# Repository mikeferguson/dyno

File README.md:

# dyno

Control code for my motor dyno

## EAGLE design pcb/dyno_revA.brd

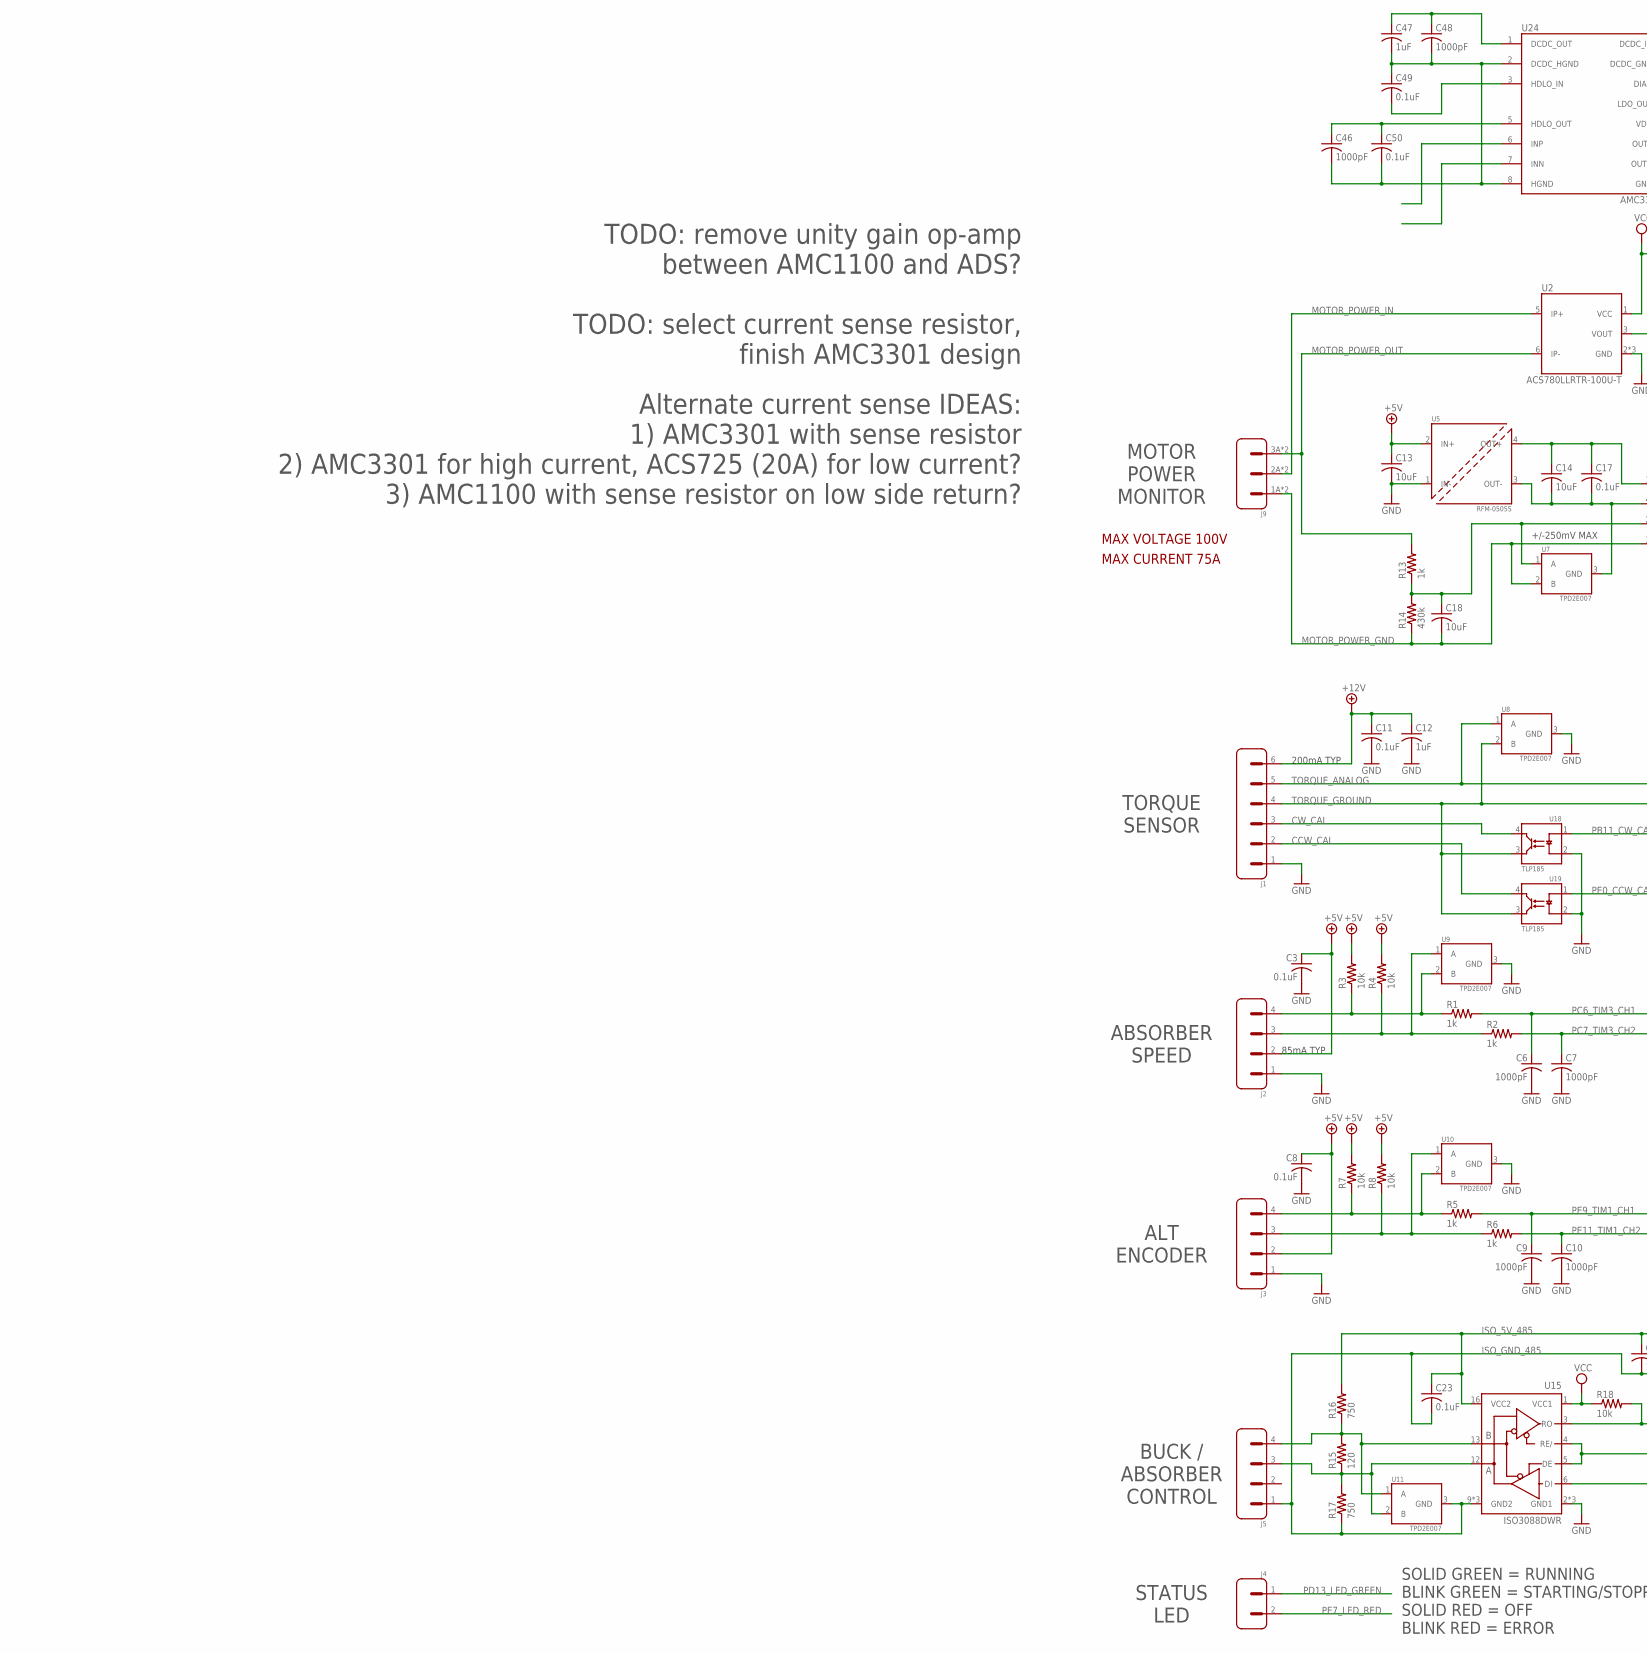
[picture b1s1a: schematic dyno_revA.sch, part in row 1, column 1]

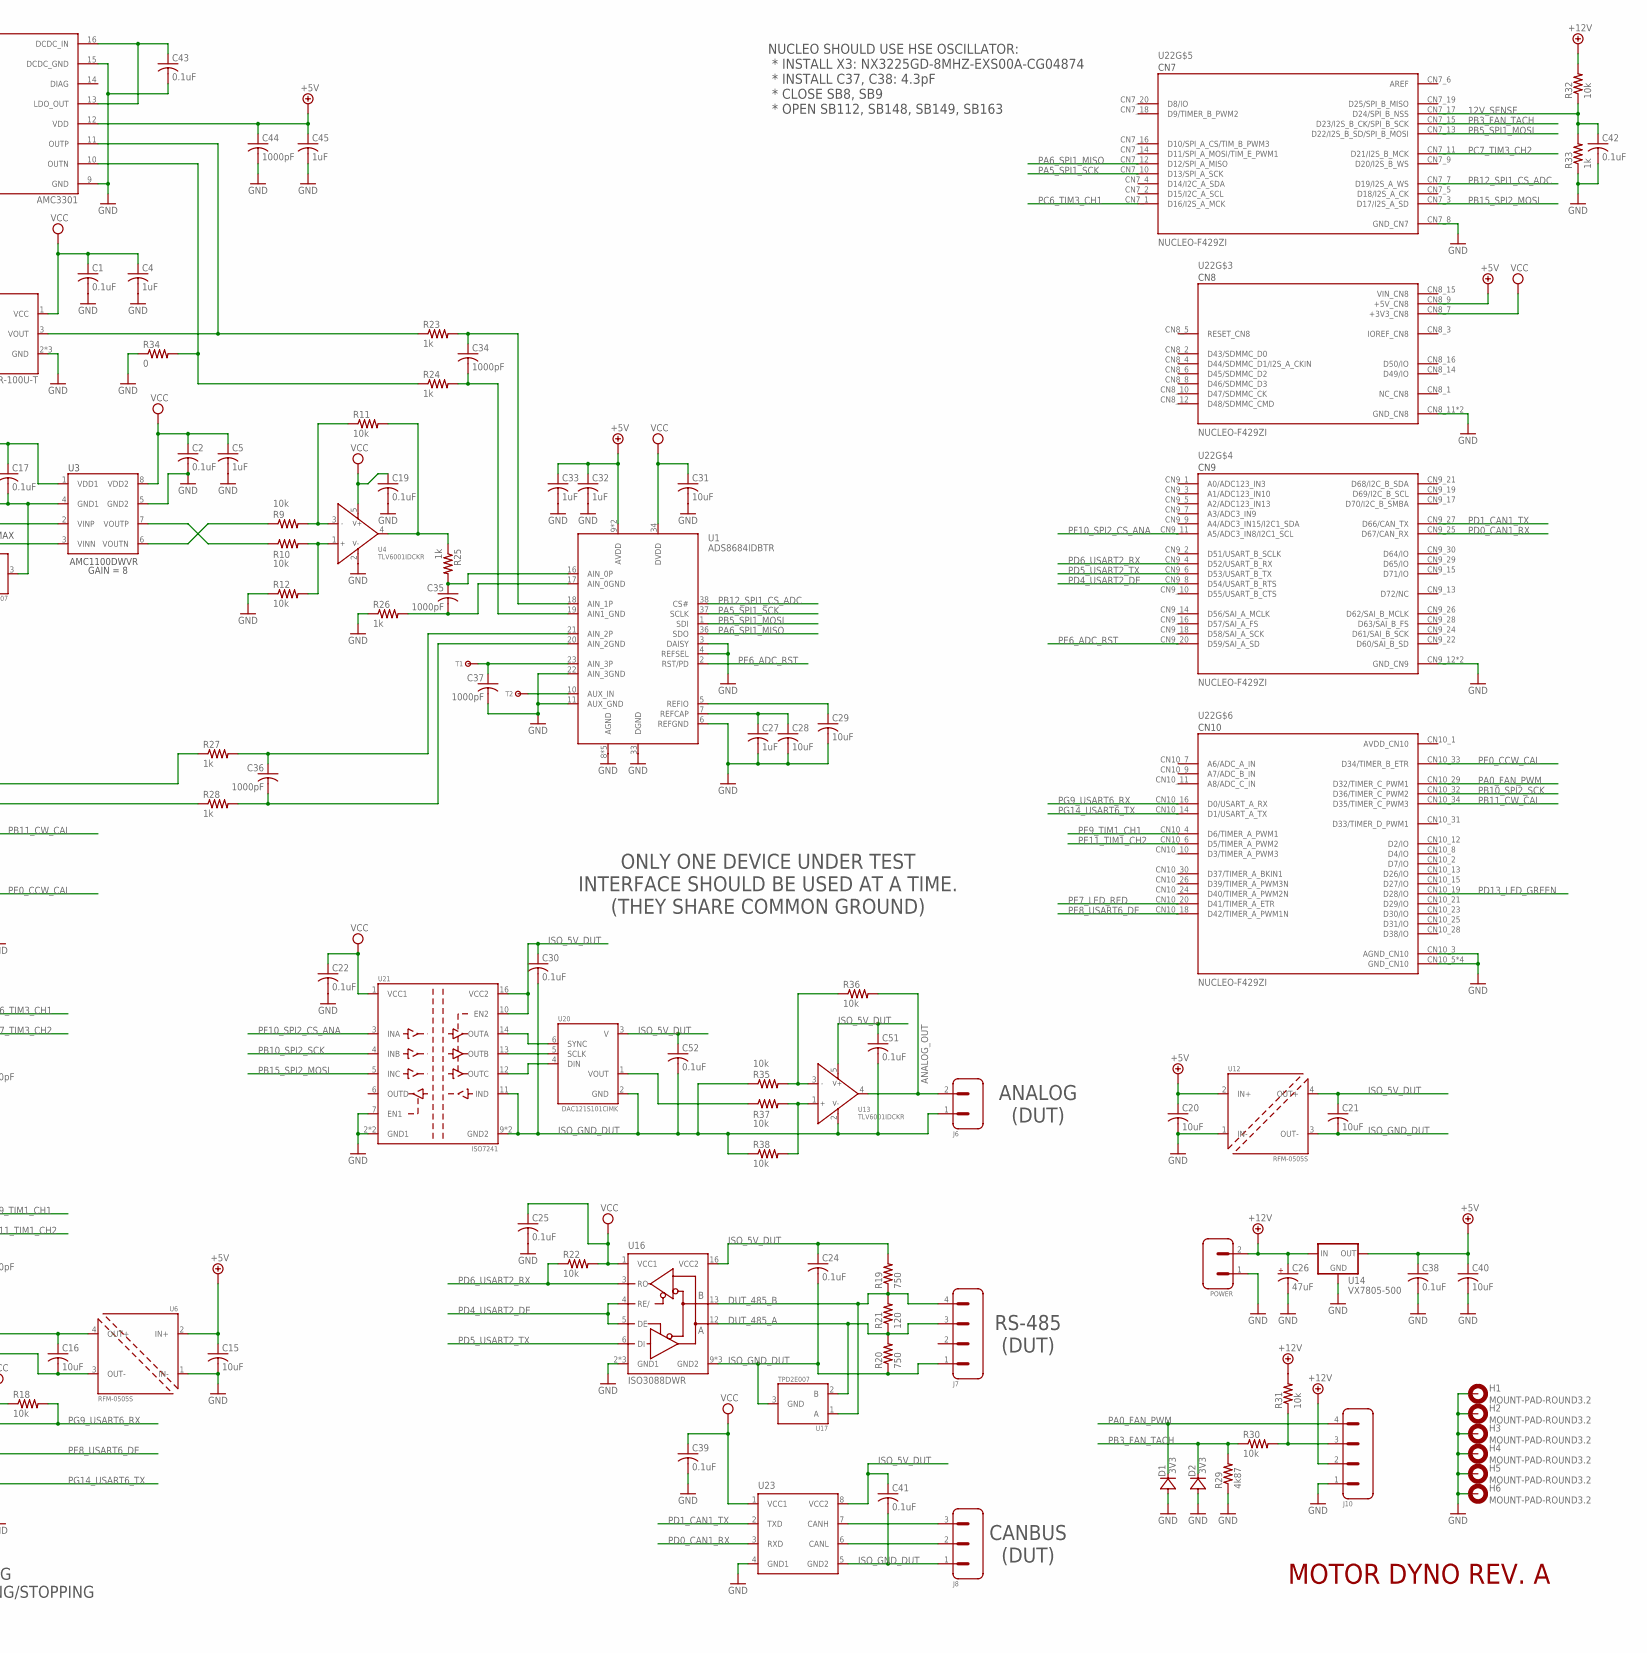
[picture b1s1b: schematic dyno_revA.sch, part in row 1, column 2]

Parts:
C1, C2, C3, C8, C11, C17, C19, C22, C23, C24, C25, C30, C38, C39, C41, C42, C43, C49, C50, C51, C52: 0.1uF; CAPC1608X90(C0603)
C4, C5, C12, C27, C32, C33, C45, C47: 1uF; CAPC1608X90(C0603)
C6, C7, C9, C10, C34, C35, C36, C37, C44, C46, C48: 1000pF; CAPC1608X90(C0603)
C13, C14, C15, C16, C18, C20, C21, C40: 10uF; CAPC2012X145
C26: 47uF; CAPAE830X850(PANA_F)
C28, C29, C31: 10uF; CAPC1608X90(C0603)
D1, D2: 3V3; SOD2513X110(SOD323)
H1, H2, H3, H4, H5, H6: MOUNT-PAD-ROUND3.2; 3,2-PAD
J1: 502584-0670
J2, J3: 502584-0470
J4, J6: 502584-0270
J5, J7: 43650-0416
J8: 43650-0316
J9: 1017532
J10: 22-23-2041
POWER: 39-29-0023; 5566-2
R1, R2, R5, R6, R13, R23, R24, R25, R26, R27, R28, R33: 1k; RESC1608X55(ERJ-0603)
R3, R4, R7, R8, R9, R10, R11, R12, R18, R22, R30, R31, R32, R35, R36, R37, R38: 10k; RESC1608X55(ERJ-0603)
R14: 430k; RESC1608X55(ERJ-0603)
R15, R21: 120; RESC1608X55(ERJ-0603)
R16, R17, R19, R20: 750; RESC1608X55(ERJ-0603)
R29: 4k87; RESC1608X55(ERJ-0603)
R34: 0; RESC1608X55(ERJ-0603)
T1, T2: TESTPAD; TEST
U1: ADS8684IDBTR; SOP50P640X120-38
U2: ACS780LLRTR-100U-T; ACS780
U3: AMC1100DWVR; SOIC127P1150X280-8
U4, U13: TLV6001IDCKR; SOT65P210X110-5
U5, U6, U12: RFM-0505S; RFM
U7, U8, U9, U10, U11, U17: TPD2E007; SOT65P210X110-3(SOT323)
U14: VX7805-500; VX78-500
U15, U16: ISO3088DWR; SOIC127P1030X265-16
U18, U19: TLP185; SOT127P700X220-4
U20: DAC121S101CIMK; SOT95P280X110-6
U21: ISO7241; SOIC127P1030X265-16
U22: NUCLEO-F429ZI; MODULE_NUCLEO-F429ZI
U23: ISO1042DWVR; SOIC127P1150X265-8N
U24: AMC3301; SOIC127P1030X265-16N

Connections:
12V_SENSE: C42.1, R32.1, R33.2, U22.CN7_17 (D24/SPI_B_NSS)
+5V: C3.1, C8.1, C13.1, C15.1, C20.1, C32.1, C33.1, C38.1, C40.1, C44.1, C45.1, J2.2, J3.2, R3.2, R4.2, R7.2, R8.2, U1.9 (AVDD), U1.30 (AVDD), U5.2 (IN+), U6.2 (IN+), U12.2 (IN+), U14.3 (OUT), U22.CN8_9 (+5V_CN8), U24.12 (VDD)
+12V: C11.1, C12.1, C26.1 (+), J1.6, J10.2, POWER.2, R31.2, R32.2, U14.1 (IN)
ABSORBER_485_A: J5.3, R15.1, R17.2, U11.2 (B), U15.12 (A)
ABSORBER_485_B: J5.4, R15.2, R16.1, U11.1 (A), U15.13 (B)
AIN_3P: C37.1, T1.T, U1.23 (AIN_3P)
ANALOG_OUT: J6.2, R36.2, U13.4 (OUT)
AREF: U22.CN7_6 (AREF)
AUX_IN: T2.T, U1.10 (AUX_IN)
AVDD_CN10: U22.CN10_1 (AVDD_CN10)
CANH: J8.3, U23.7 (CANH)
CANL: J8.2, U23.6 (CANL)
CCW_CAL: J1.2, U19.4 (COLL)
CW_CAL: J1.3, U18.4 (COLL)
DUT_485_A: J7.3, R20.2, R21.1, U16.12 (A), U17.2 (B)
DUT_485_B: J7.4, R19.1, R21.2, U16.13 (B), U17.1 (A)
ENC_A: J3.4, R5.1, R7.1, U10.2 (B)
ENC_B: J3.3, R6.1, R8.1, U10.1 (A)
GND: C1.2, C2.2, C3.2, C4.2, C5.2, C6.2, C7.2, C8.2, C9.2, C10.2, C11.2, C12.2, C13.2, C15.2, C19.2, C20.2, C22.2, C25.2, C26.2 (-), C27.2, C28.2, C29.2, C31.2, C32.2, C33.2, C37.2, C38.2, C39.2, C40.2, C42.2, C43.2, C44.2, C45.2, D1.2 (A), D2.2 (A), H1.B3,2, H2.B3,2, H3.B3,2, H4.B3,2, H5.B3,2, H6.B3,2, J1.1, J2.1, J3.1, J10.1, POWER.1, R12.1, R26.1, R29.1, R33.1, R34.1, U1.3 (DAISY), U1.4 (REFSEL), U1.6 (REFGND), U1.8 (AGND), U1.11 (AUX_GND), U1.22 (AIN_3GND), U1.28 (AGND), U1.29 (AGND), U1.31 (AGND), U1.32 (AGND), U1.33 (DGND), U2.2 (GND), U2.4 (GND), U2.7 (GND), U3.5 (GND2), U4.2 (V-), U5.1 (IN-), U6.1 (IN-), U8.3 (GND), U9.3 (GND), U10.3 (GND), U12.1 (IN-), U14.2 (GND), U15.2 (GND1), U15.7 (GND1), U15.8 (GND1), U16.2 (GND1), U16.7 (GND1), U16.8 (GND1), U18.2 (C), U19.2 (C), U21.2 (GND1), U21.7 (EN1), U21.8 (GND1), U22.CN7_8 (GND_CN7), U22.CN8_11 (GND_CN8), U22.CN8_13 (GND_CN8), U22.CN9_12 (GND_CN9), U22.CN9_23 (GND_CN9), U22.CN10_3 (AGND_CN10), U22.CN10_5 (GND_CN10), U22.CN10_17 (GND_CN10), U22.CN10_22 (GND_CN10), U22.CN10_27 (GND_CN10), U23.4 (GND1), U24.9 (GND), U24.15 (DCDC_GND)
ISENSE_OUT: R23.1, U2.3 (VOUT), U24.11 (OUTP)
ISO_5V_485: C16.1, C23.1, R16.2, U6.4 (OUT+), U15.16 (VCC2)
ISO_5V_DUT: C21.1, C24.1, C30.1, C41.1, C51.1, C52.1, R19.2, U12.4 (OUT+), U13.5 (V+), U16.16 (VCC2), U20.3 (V), U21.10 (EN2), U21.16 (VCC2), U23.8 (VCC2)
ISO_5V_M: C14.1, C17.1, U3.1 (VDD1), U5.4 (OUT+)
ISO_GND_485: C16.2, C23.2, J5.1, R17.1, U6.3 (OUT-), U11.3 (GND), U15.9 (GND2), U15.10 (GND2), U15.15 (GND2)
ISO_GND_DUT: C21.2, C24.2, C30.2, C41.2, C51.2, C52.2, J6.1, J7.1, J8.1, R20.1, R35.1, R38.1, U12.3 (OUT-), U13.2 (V-), U16.9 (GND2), U16.10 (GND2), U16.15 (GND2), U17.3 (GND), U20.2 (GND), U21.9 (GND2), U21.11 (IND), U21.15 (GND2), U23.5 (GND2)
ISO_GND_M: C14.2, C17.2, U3.4 (GND1), U5.3 (OUT-), U7.3 (GND)
MOTOR_POWER_GND: C18.2, J9.1A (1), J9.1B (1), R14.1, U3.3 (VINN), U7.2 (B)
MOTOR_POWER_IN: J9.2A (2), J9.2B (2), U2.5 (IP+)
MOTOR_POWER_OUT: J9.3A (3), J9.3B (3), R13.2, U2.6 (IP-)
unnamed: J10.3, R30.2, R31.1
unnamed: C43.1, U24.13 (LDO_OUT), U24.16 (DCDC_IN)
unnamed: R10.2, R12.2, U4.1 (+)
unnamed: R9.2, R11.1, U4.3 (-)
unnamed: R24.1, R34.2, U24.10 (OUTN)
unnamed: C35.2, R26.2, U1.17 (AIN_0GND)
unnamed: C35.1, R25.2, U1.16 (AIN_0P)
unnamed: R10.1, U3.7 (VOUTP)
unnamed: R37.1, U20.1 (VOUT)
unnamed: U20.6 (SYNC), U21.14 (OUTA)
unnamed: U20.5 (SCLK), U21.13 (OUTB)
unnamed: U20.4 (DIN), U21.12 (OUTC)
unnamed: R9.1, U3.6 (VOUTN)
unnamed: C34.1, R23.2, U1.18 (AIN_1P)
unnamed: C34.2, R24.2, U1.19 (AIN1_GND)
unnamed: C46.1, C50.1, U24.5 (HDLO_OUT)
unnamed: C46.2, C47.2, C48.2, C49.1, C50.2, U24.2 (DCDC_HGND), U24.8 (HGND)
unnamed: C47.1, C48.1, U24.1 (DCDC_OUT)
unnamed: C49.2, U24.3 (HDLO_IN)
unnamed: R37.2, R38.2, U13.1 (+)
unnamed: R35.2, R36.1, U13.3 (-)
PA0_FAN_PWM: D1.1 (C), J10.4, U22.CN10_29 (D32/TIMER_C_PWM1)
PA5_SPI1_SCK: U1.37 (SCLK), U22.CN7_10 (D13/SPI_A_SCK)
PA6_SPI1_MISO: U1.36 (SDO), U22.CN7_12 (D12/SPI_A_MISO)
PB3_FAN_TACH: D2.1 (C), R29.2, R30.1, U22.CN7_15 (D23/I2S_B_CK/SPI_B_SCK)
PB5_SPI1_MOSI: U1.1 (SDI), U22.CN7_13 (D22/I2S_B_SD/SPI_B_MOSI)
PB10_SPI2_SCK: U21.4 (INB), U22.CN10_32 (D36/TIMER_C_PWM2)
PB11_CW_CAL: U18.1 (A), U22.CN10_34 (D35/TIMER_C_PWM3)
PB12_SPI1_CS_ADC: U1.38 (CS#), U22.CN7_7 (D19/I2S_A_WS)
PB15_SPI2_MOSI: U21.5 (INC), U22.CN7_3 (D17/I2S_A_SD)
PC6_TIM3_CH1: C6.1, R1.2, U22.CN7_1 (D16/I2S_A_MCK)
PC7_TIM3_CH2: C7.1, R2.2, U22.CN7_11 (D21/I2S_B_MCK)
PD0_CAN1_RX: U22.CN9_25 (D67/CAN_RX), U23.3 (RXD)
PD1_CAN1_TX: U22.CN9_27 (D66/CAN_TX), U23.2 (TXD)
PD4_USART2_DE: U16.4 (RE/), U16.5 (DE), U22.CN9_8 (D54/USART_B_RTS)
PD5_USART2_TX: U16.6 (DI), U22.CN9_6 (D53/USART_B_TX)
PD6_USART2_RX: R22.1, U16.3 (RO), U22.CN9_4 (D52/USART_B_RX)
PD13_LED_GREEN: J4.1, U22.CN10_19 (D28/IO)
PE0_CCW_CAL: U19.1 (A), U22.CN10_33 (D34/TIMER_B_ETR)
PE6_ADC_RST: U1.2 (RST/PD), U22.CN9_20 (D59/SAI_A_SD)
PE7_LED_RED: J4.2, U22.CN10_20 (D41/TIMER_A_ETR)
PE8_USART6_DE: U15.4 (RE/), U15.5 (DE), U22.CN10_18 (D42/TIMER_A_PWM1N)
PE9_TIM1_CH1: C9.1, R5.2, U22.CN10_4 (D6/TIMER_A_PWM1)
PE11_TIM1_CH2: C10.1, R6.2, U22.CN10_6 (D5/TIMER_A_PWM2)
PF10_SPI2_CS_ANA: U21.3 (INA), U22.CN9_11 (A5/ADC3_IN8/I2C1_SCL)
PG9_USART6_RX: R18.2, U15.3 (RO), U22.CN10_16 (D0/USART_A_RX)
PG14_USART6_TX: U15.6 (DI), U22.CN10_14 (D1/USART_A_TX)
REFCAP: C27.1, C28.1, U1.7 (REFCAP)
REFIO: C29.1, U1.5 (REFIO)
SENSE_VOLTAGE: C18.1, R13.1, R14.2, U3.2 (VINP), U7.1 (A)
SPEED_A: J2.4, R1.1, R3.1, U9.2 (B)
SPEED_B: J2.3, R2.1, R4.1, U9.1 (A)
TAF: C36.1, R27.2, U1.21 (AIN_2P)
TGF: C36.2, R28.2, U1.20 (AIN_2GND)
TORQUE_ANALOG: J1.5, R27.1, U8.1 (A)
TORQUE_GROUND: J1.4, R28.1, U8.2 (B), U18.3 (EMIT), U19.3 (EMIT)
VCC: C1.1, C2.1, C4.1, C5.1, C19.1, C22.1, C25.1, C31.1, C39.1, R18.1, R22.2, U1.34 (DVDD), U2.1 (VCC), U3.8 (VDD2), U4.5 (V+), U15.1 (VCC1), U16.1 (VCC1), U21.1 (VCC1), U22.CN8_7 (+3V3_CN8), U23.1 (VCC1)
VIN_CN8: U22.CN8_15 (VIN_CN8)
VSENSE_OUT: R11.2, R25.1, U4.4 (OUT)

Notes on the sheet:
MOTOR DYNO REV. A
TORQUE SENSOR
ABSORBER SPEED
85mA TYP
ALT ENCODER
200mA TYP
MOTOR POWER MONITOR
RS-485 (DUT)
BUCK / ABSORBER CONTROL
ONLY ONE DEVICE UNDER TEST INTERFACE SHOULD BE USED AT A TIME. (THEY SHARE COMMON GROUND)
ANALOG (DUT)
STATUS LED
SOLID GREEN = RUNNING BLINK GREEN = STARTING/STOPPING SOLID RED = OFF BLINK RED = ERROR
MAX VOLTAGE 100V
MAX CURRENT 75A
NUCLEO SHOULD USE HSE OSCILLATOR: * INSTALL X3: NX3225GD-8MHZ-EXS00A-CG04874 * INSTALL C37, C38: 4.3pF * CLOSE SB8, SB9 * OPEN SB112, SB148, SB149, SB163
CANBUS (DUT)
GAIN = 8
+/-250mV MAX
TODO: select current sense resistor, finish AMC3301 design
TODO: remove unity gain op-amp between AMC1100 and ADS?
Alternate current sense IDEAS: 1) AMC3301 with sense resistor 2) AMC3301 for high current, ACS725 (20A) for low current? 3) AMC1100 with sense resistor on low side return?

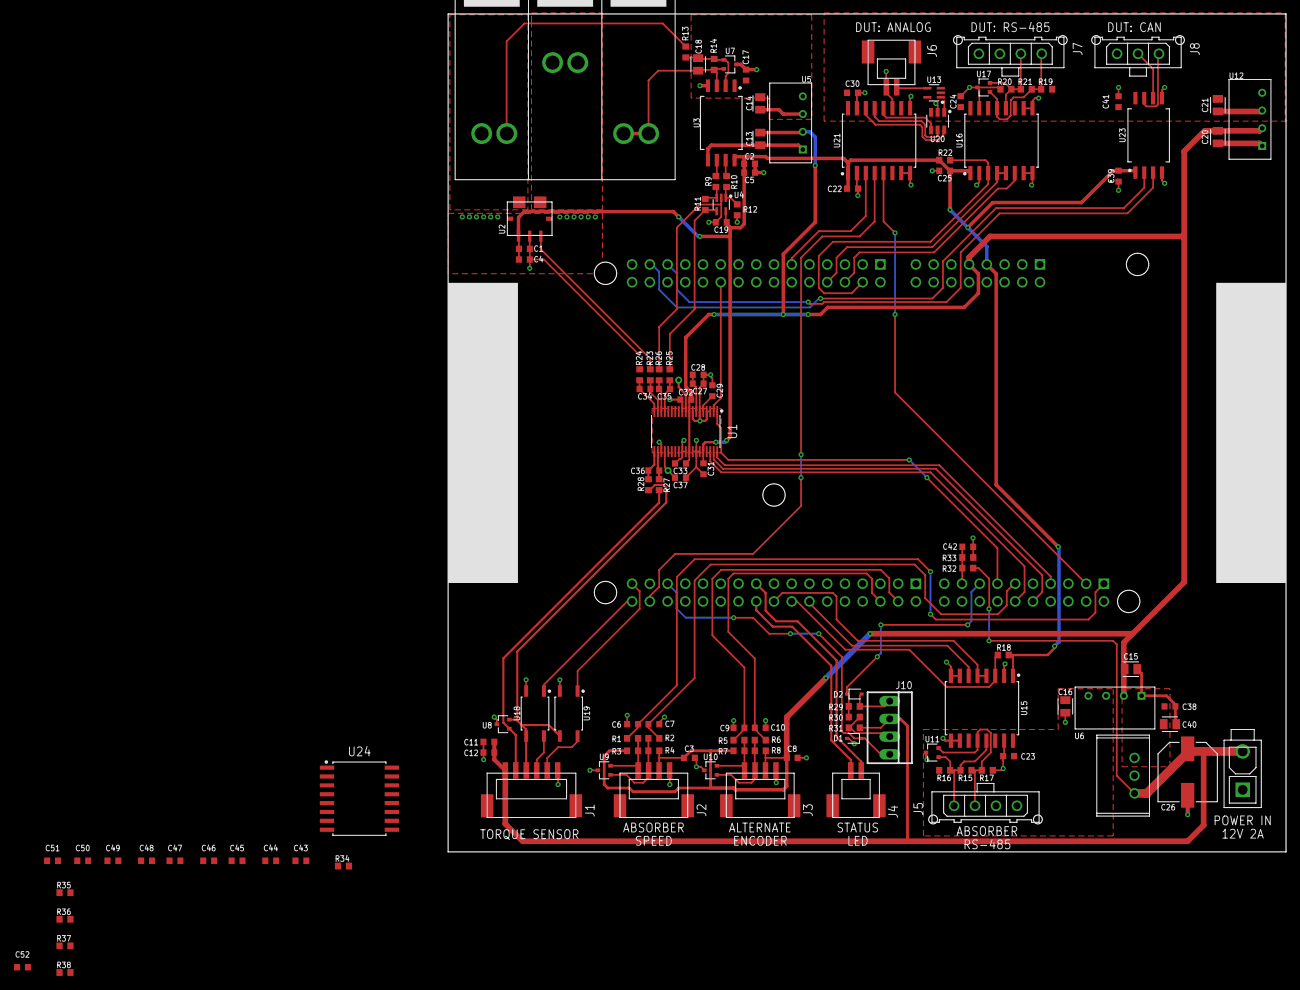
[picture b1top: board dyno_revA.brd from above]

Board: 2 copper layers, 120.0 x 120.0 mm, 135 parts (0 on the bottom side), 85 nets.

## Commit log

2023-01-18 migrate dyno interface
2023-01-18 check in first pass of gui
2023-03-02 check in WIP
2023-03-02 check in temp cube config
2023-03-02 improved system test
2023-04-26 not quite working
2023-05-04 additional work - still not happy
2023-05-04 note repo
2024-12-19 updates for ubuntu noble
2024-12-19 noble updates
2024-12-19 mostly working
2024-12-19 add support for VESC-based absorber (#1)
    this doesn't work great - the velocity mode is best, road load is sketchy due to inability to control motor at slow velocities. lower limits appear to be ~13.5 rad/s and 0.12 Nm.
2024-12-20 documentation
2024-12-30 add basic ros2 interface
2024-12-30 reorganize a bit
2024-12-30 fix button functionality
2025-01-01 basic test harness
2025-01-02 fix indentation issue
2025-01-02 firmware is updated
2025-01-02 improve stability of visualization
2025-01-02 refactor commands
2025-01-02 add offset calibration
2025-01-10 avoid circular references
2025-01-10 implement uncalibrated control of powder brake
2025-01-11 remove outdated info
2025-01-14 calibrate powder brake output
2025-01-20 small reorg before adding more DUT utilities
2025-01-20 add load brake ROS topic, filtering option for DUT client
2025-01-20 recalibrate load brake at higher torques - this works up to 25Nm
2025-01-20 add first pass of efficiency plot client
2025-01-21 add file save/load, power limit
2025-01-21 fix bugs in logging
2025-07-11 minor updates to efficiency script
2025-08-22 add configurable levels
2025-09-17 disable absorber when stopped, on exit
2025-09-22 add option to plot efficiency
2025-09-22 add support for comments in log file
2025-09-22 use argparse, add gearing option
